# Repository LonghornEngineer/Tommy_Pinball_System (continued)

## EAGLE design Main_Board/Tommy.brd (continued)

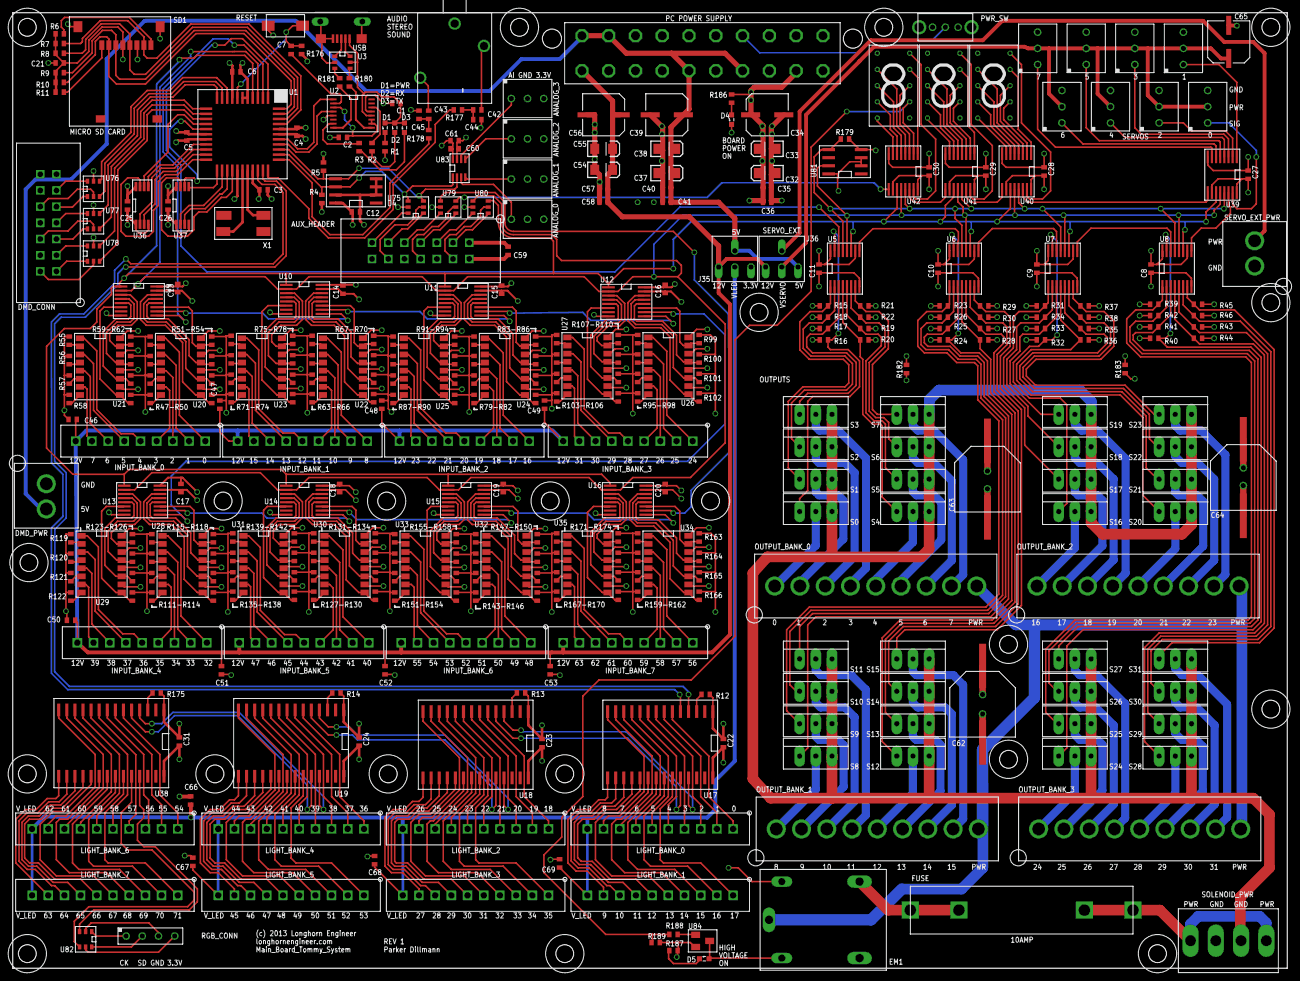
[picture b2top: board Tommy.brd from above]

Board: 4 copper layers, 199.9 x 149.9 mm, 419 parts (0 on the bottom side), 478 nets.

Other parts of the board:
U$2, U$3, U$4, U$5, U$6, U$7, U$8, U$9, U$10, U$11, U$12, U$13, U$14, U$15, U$16, U$17, U$18, U$19, U$20, U$21, U$22: MOUNT_HOLE_2.8MM

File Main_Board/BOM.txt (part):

Partlist

Exported from Tommy.sch at 11/21/2013 11:01:43 AM

EAGLE Version 6.3.0 Copyright (c) 1988-2012 CadSoft

Assembly variant: 

Part            Value                Device                          Package                Library              Sheet

ANALOG_0                             PH_1X03HEADER_PTH               HEADER_01X03_PTH       PP_Connectors        1
ANALOG_1                             PH_1X03HEADER_PTH               HEADER_01X03_PTH       PP_Connectors        1
ANALOG_2                             PH_1X03HEADER_PTH               HEADER_01X03_PTH       PP_Connectors        1
ANALOG_3                             PH_1X03HEADER_PTH               HEADER_01X03_PTH       PP_Connectors        1
AUDIO           161-3507-E           TRS_JACK161-3507-E              161-3507-E             PP_Connectors        1
AUX             103169-5             PH_2X07PTH                      HEADER_02X07_PTH       PP_Connectors        1
C1              .1uF                 CAPACITOR_NON_POLAR0402         0402                   PP_Passives          1
C2              .1uF                 CAPACITOR_NON_POLAR0402         0402                   PP_Passives          1
C3              .1uF                 CAPACITOR_NON_POLAR0402         0402                   PP_Passives          1
C4              .1uF                 CAPACITOR_NON_POLAR0402         0402                   PP_Passives          1
C5              .1uF                 CAPACITOR_NON_POLAR0402         0402                   PP_Passives          1
C6              .1uF                 CAPACITOR_NON_POLAR0402         0402                   PP_Passives          1
C7              .1uF                 CAPACITOR_NON_POLAR0402         0402                   PP_Passives          1
C8              .1uF                 CAPACITOR_NON_POLAR0402         0402                   PP_Passives          1
C9              .1uF                 CAPACITOR_NON_POLAR0402         0402                   PP_Passives          1
C10             .1uF                 CAPACITOR_NON_POLAR0402         0402                   PP_Passives          1
C11             .1uF                 CAPACITOR_NON_POLAR0402         0402                   PP_Passives          1
C12             .1uF                 CAPACITOR_NON_POLAR0402         0402                   PP_Passives          1
C13             .1uF                 CAPACITOR_NON_POLAR0402         0402                   PP_Passives          1
C14             .1uF                 CAPACITOR_NON_POLAR0402         0402                   PP_Passives          1
C15             .1uF                 CAPACITOR_NON_POLAR0402         0402                   PP_Passives          1
C16             .1uF                 CAPACITOR_NON_POLAR0402         0402                   PP_Passives          1
C17             .1uF                 CAPACITOR_NON_POLAR0402         0402                   PP_Passives          1
C18             .1uF                 CAPACITOR_NON_POLAR0402         0402                   PP_Passives          1
C19             .1uF                 CAPACITOR_NON_POLAR0402         0402                   PP_Passives          1
C20             .1uF                 CAPACITOR_NON_POLAR0402         0402                   PP_Passives          1
C21             .1uF                 CAPACITOR_NON_POLAR0402         0402                   PP_Passives          1
C22             .1uF                 CAPACITOR_NON_POLAR0402         0402                   PP_Passives          1
C23             .1uF                 CAPACITOR_NON_POLAR0402         0402                   PP_Passives          1
C24             .1uF                 CAPACITOR_NON_POLAR0402         0402                   PP_Passives          1
C25             .1uF                 CAPACITOR_NON_POLAR0402         0402                   PP_Passives          1
C26             .1uF                 CAPACITOR_NON_POLAR0402         0402                   PP_Passives          1
C27             .1uF                 CAPACITOR_NON_POLAR0402         0402                   PP_Passives          1
C28             .1uF                 CAPACITOR_NON_POLAR0402         0402                   PP_Passives          1
C29             .1uF                 CAPACITOR_NON_POLAR0402         0402                   PP_Passives          1
C30             .1uF                 CAPACITOR_NON_POLAR0402         0402                   PP_Passives          1
C31             .1uF                 CAPACITOR_NON_POLAR0402         0402                   PP_Passives          1
C32             2.2uF                CAPACITOR_POLARIZED1206         1206_POLARIZED         PP_Passives          1
C33             10uF                 CAPACITOR_POLARIZED1206         1206_POLARIZED         PP_Passives          1
C34             100uF                CAPACITOR_POLARIZED6.3MM_SMD    6.3MM_CAP_SMD          PP_Passives          1
C35             1uF                  CAPACITOR_NON_POLAR0402         0402                   PP_Passives          1
C36             .1uF                 CAPACITOR_NON_POLAR0402         0402                   PP_Passives          1
C37             2.2uF                CAPACITOR_POLARIZED1206         1206_POLARIZED         PP_Passives          1
C38             10uF                 CAPACITOR_POLARIZED1206         1206_POLARIZED         PP_Passives          1
C39             100uF                CAPACITOR_POLARIZED6.3MM_SMD    6.3MM_CAP_SMD          PP_Passives          1
C40             1uF                  CAPACITOR_NON_POLAR0402         0402                   PP_Passives          1
C41             .1uF                 CAPACITOR_NON_POLAR0402         0402                   PP_Passives          1
C42             1uF                  CAPACITOR_NON_POLAR0402         0402                   PP_Passives          1
C43             1uF                  CAPACITOR_NON_POLAR0402         0402                   PP_Passives          1
C44             .1uF                 CAPACITOR_NON_POLAR0402         0402                   PP_Passives          1
C45             .1uF                 CAPACITOR_NON_POLAR0402         0402                   PP_Passives          1
C46             .1uF                 CAPACITOR_NON_POLAR0402         0402                   PP_Passives          1
C47             .1uF                 CAPACITOR_NON_POLAR0402         0402                   PP_Passives          1
C48             .1uF                 CAPACITOR_NON_POLAR0402         0402                   PP_Passives          1
C49             .1uF                 CAPACITOR_NON_POLAR0402         0402                   PP_Passives          1
C50             .1uF                 CAPACITOR_NON_POLAR0402         0402                   PP_Passives          1
C51             .1uF                 CAPACITOR_NON_POLAR0402         0402                   PP_Passives          1
C52             .1uF                 CAPACITOR_NON_POLAR0402         0402                   PP_Passives          1
C53             .1uF                 CAPACITOR_NON_POLAR0402         0402                   PP_Passives          1
C54             2.2uF                CAPACITOR_POLARIZED1206         1206_POLARIZED         PP_Passives          1
C55             10uF                 CAPACITOR_POLARIZED1206         1206_POLARIZED         PP_Passives          1
C56             100uF                CAPACITOR_POLARIZED6.3MM_SMD    6.3MM_CAP_SMD          PP_Passives          1
C57             1uF                  CAPACITOR_NON_POLAR0402         0402                   PP_Passives          1
C58             .1uF                 CAPACITOR_NON_POLAR0402         0402                   PP_Passives          1
C59             .1uF                 CAPACITOR_NON_POLAR0402         0402                   PP_Passives          1
C60             1uF                  CAPACITOR_NON_POLAR0402         0402                   PP_Passives          1
C61             .1uF                 CAPACITOR_NON_POLAR0402         0402                   PP_Passives          1
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
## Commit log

2013-10-22 Pushing first REV_0 board and schematic files
2013-10-22 Pushing REV_1 to the repo
2013-10-22 Added the FT230X_Template
2013-11-21 Added more files
    Bom.txt, Pinout of the propeller and new images of the layouts. Updated
    ReadME.
2013-11-21 Removed header from Pinout File
2013-11-21 Testing a change
2013-11-21 Changed whitespace so it displays correctly.
2014-04-09 Update to CC-BY-SA License.
